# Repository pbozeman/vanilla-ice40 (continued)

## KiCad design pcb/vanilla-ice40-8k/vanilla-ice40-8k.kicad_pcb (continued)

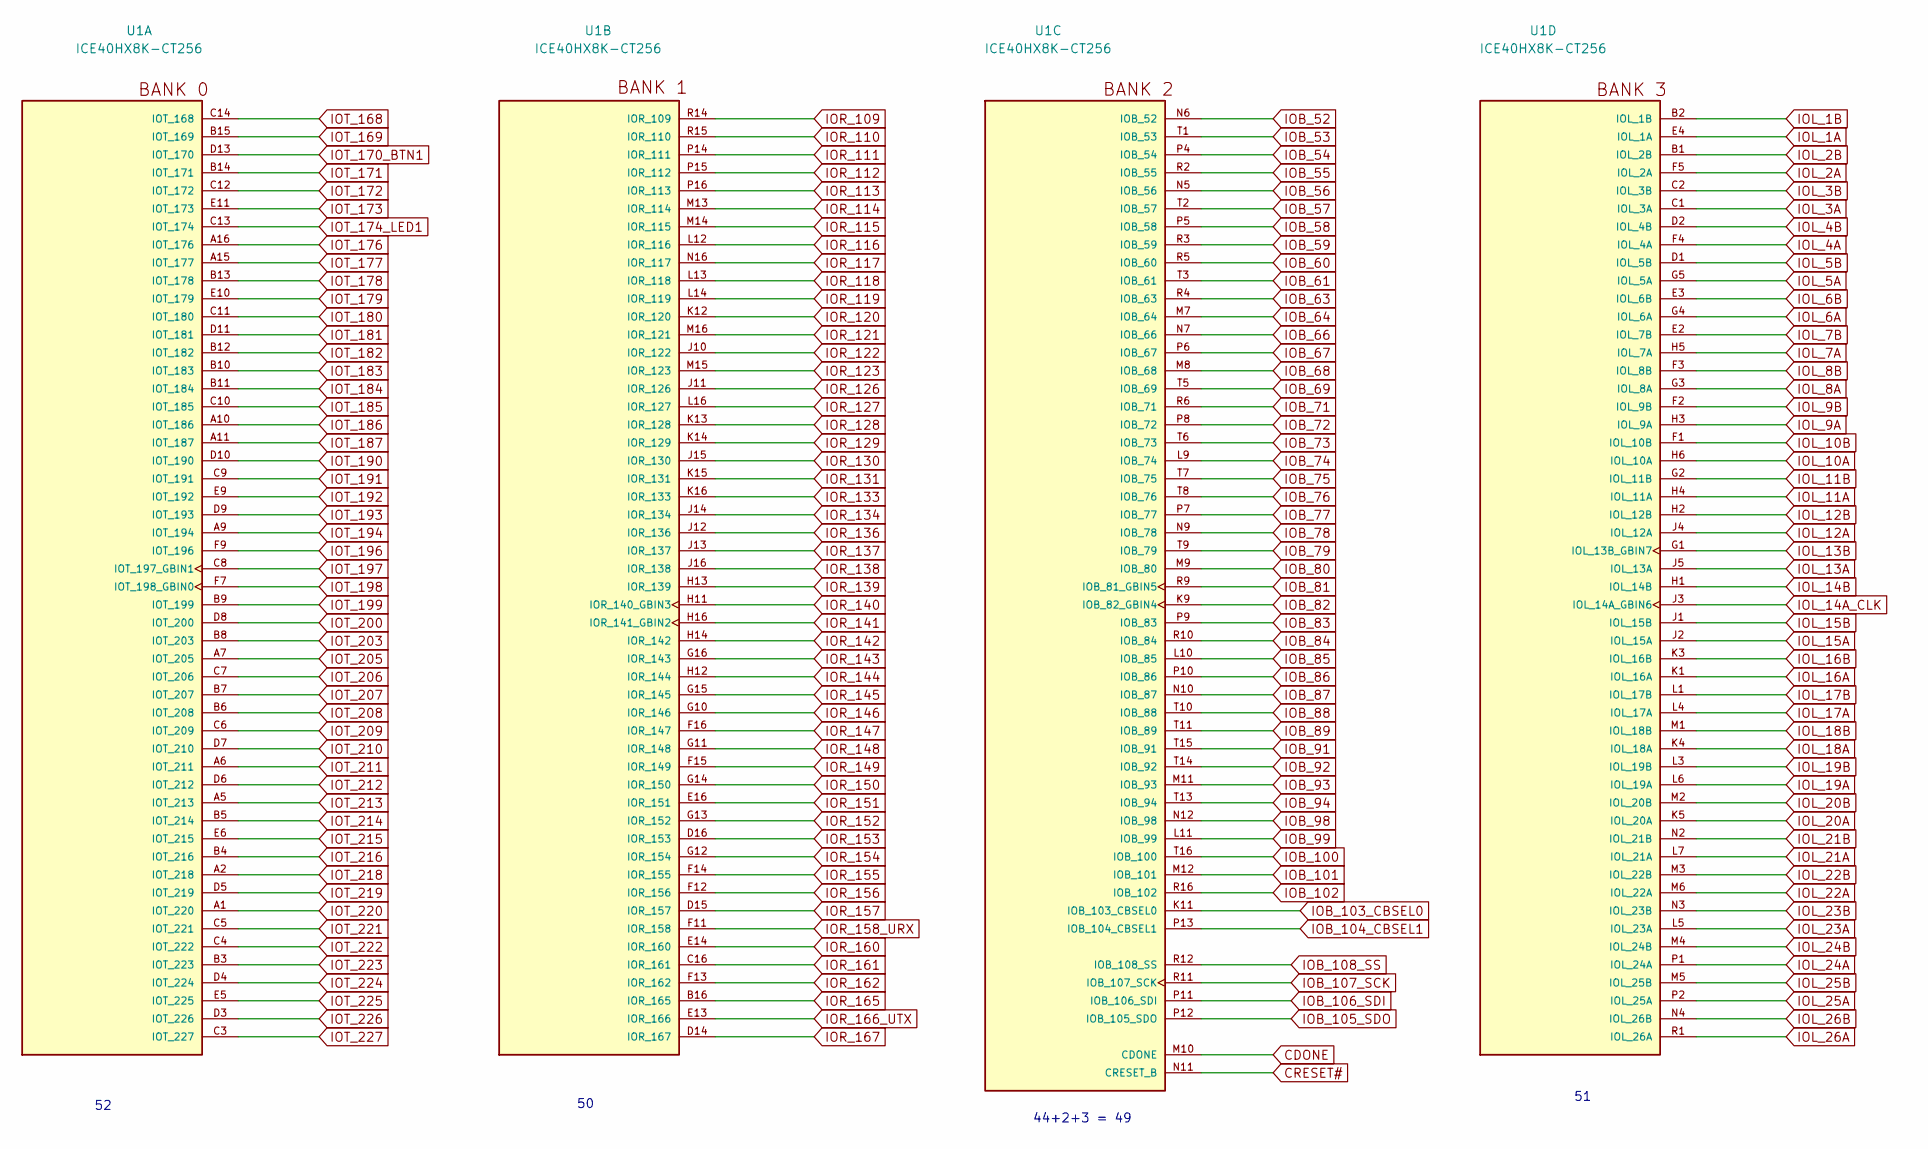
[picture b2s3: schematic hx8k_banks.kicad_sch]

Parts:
U1: ICE40HX8K-CT256; BGA256C80P16X16_1400X1400X170; Digi-Key Part Number 220-1575-ND

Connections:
CDONE: U1.M10 (CDONE); also elsewhere on the board
CRESET#: U1.N11 (CRESET_B); also elsewhere on the board
IOB_52: U1.N6 (IOB_52); also elsewhere on the board
IOB_53: U1.T1 (IOB_53); also elsewhere on the board
IOB_54: U1.P4 (IOB_54); also elsewhere on the board
IOB_55: U1.R2 (IOB_55); also elsewhere on the board
IOB_56: U1.N5 (IOB_56); also elsewhere on the board
IOB_57: U1.T2 (IOB_57); also elsewhere on the board
IOB_58: U1.P5 (IOB_58); also elsewhere on the board
IOB_59: U1.R3 (IOB_59); also elsewhere on the board
IOB_60: U1.R5 (IOB_60); also elsewhere on the board
IOB_61: U1.T3 (IOB_61); also elsewhere on the board
IOB_63: U1.R4 (IOB_63); also elsewhere on the board
IOB_64: U1.M7 (IOB_64); also elsewhere on the board
IOB_66: U1.N7 (IOB_66); also elsewhere on the board
IOB_67: U1.P6 (IOB_67); also elsewhere on the board
IOB_68: U1.M8 (IOB_68); also elsewhere on the board
IOB_69: U1.T5 (IOB_69); also elsewhere on the board
IOB_71: U1.R6 (IOB_71); also elsewhere on the board
IOB_72: U1.P8 (IOB_72); also elsewhere on the board
IOB_73: U1.T6 (IOB_73); also elsewhere on the board
IOB_74: U1.L9 (IOB_74); also elsewhere on the board
IOB_75: U1.T7 (IOB_75); also elsewhere on the board
IOB_76: U1.T8 (IOB_76); also elsewhere on the board
IOB_77: U1.P7 (IOB_77); also elsewhere on the board
IOB_78: U1.N9 (IOB_78); also elsewhere on the board
IOB_79: U1.T9 (IOB_79); also elsewhere on the board
IOB_80: U1.M9 (IOB_80); also elsewhere on the board
IOB_81: U1.R9 (IOB_81_GBIN5); also elsewhere on the board
IOB_82: U1.K9 (IOB_82_GBIN4); also elsewhere on the board
IOB_83: U1.P9 (IOB_83); also elsewhere on the board
IOB_84: U1.R10 (IOB_84); also elsewhere on the board
IOB_85: U1.L10 (IOB_85); also elsewhere on the board
IOB_86: U1.P10 (IOB_86); also elsewhere on the board
IOB_87: U1.N10 (IOB_87); also elsewhere on the board
IOB_88: U1.T10 (IOB_88); also elsewhere on the board
IOB_89: U1.T11 (IOB_89); also elsewhere on the board
IOB_91: U1.T15 (IOB_91); also elsewhere on the board
IOB_92: U1.T14 (IOB_92); also elsewhere on the board
IOB_93: U1.M11 (IOB_93); also elsewhere on the board
IOB_94: U1.T13 (IOB_94); also elsewhere on the board
IOB_98: U1.N12 (IOB_98); also elsewhere on the board
IOB_99: U1.L11 (IOB_99); also elsewhere on the board
IOB_100: U1.T16 (IOB_100); also elsewhere on the board
IOB_101: U1.M12 (IOB_101); also elsewhere on the board
IOB_102: U1.R16 (IOB_102); also elsewhere on the board
IOB_103_CBSEL0: U1.K11 (IOB_103_CBSEL0); also elsewhere on the board
IOB_104_CBSEL1: U1.P13 (IOB_104_CBSEL1); also elsewhere on the board
IOB_105_SDO: U1.P12 (IOB_105_SDO); also elsewhere on the board
IOB_106_SDI: U1.P11 (IOB_106_SDI); also elsewhere on the board
IOB_107_SCK: U1.R11 (IOB_107_SCK); also elsewhere on the board
IOB_108_SS: U1.R12 (IOB_108_SS); also elsewhere on the board
IOL_1A: U1.E4 (IOL_1A); also elsewhere on the board
IOL_1B: U1.B2 (IOL_1B); also elsewhere on the board
IOL_2A: U1.F5 (IOL_2A); also elsewhere on the board
IOL_2B: U1.B1 (IOL_2B); also elsewhere on the board
IOL_3A: U1.C1 (IOL_3A); also elsewhere on the board
IOL_3B: U1.C2 (IOL_3B); also elsewhere on the board
IOL_4A: U1.F4 (IOL_4A); also elsewhere on the board
IOL_4B: U1.D2 (IOL_4B); also elsewhere on the board
IOL_5A: U1.G5 (IOL_5A); also elsewhere on the board
IOL_5B: U1.D1 (IOL_5B); also elsewhere on the board
IOL_6A: U1.G4 (IOL_6A); also elsewhere on the board
IOL_6B: U1.E3 (IOL_6B); also elsewhere on the board
IOL_7A: U1.H5 (IOL_7A); also elsewhere on the board
IOL_7B: U1.E2 (IOL_7B); also elsewhere on the board
IOL_8A: U1.G3 (IOL_8A); also elsewhere on the board
IOL_8B: U1.F3 (IOL_8B); also elsewhere on the board
IOL_9A: U1.H3 (IOL_9A); also elsewhere on the board
IOL_9B: U1.F2 (IOL_9B); also elsewhere on the board
IOL_10A: U1.H6 (IOL_10A); also elsewhere on the board
IOL_10B: U1.F1 (IOL_10B); also elsewhere on the board
IOL_11A: U1.H4 (IOL_11A); also elsewhere on the board
IOL_11B: U1.G2 (IOL_11B); also elsewhere on the board
IOL_12A: U1.J4 (IOL_12A); also elsewhere on the board
IOL_12B: U1.H2 (IOL_12B); also elsewhere on the board
IOL_13A: U1.J5 (IOL_13A); also elsewhere on the board
IOL_13B: U1.G1 (IOL_13B_GBIN7); also elsewhere on the board
IOL_14A_CLK: U1.J3 (IOL_14A_GBIN6); also elsewhere on the board
IOL_14B: U1.H1 (IOL_14B); also elsewhere on the board
IOL_15A: U1.J2 (IOL_15A); also elsewhere on the board
IOL_15B: U1.J1 (IOL_15B); also elsewhere on the board
IOL_16A: U1.K1 (IOL_16A); also elsewhere on the board
IOL_16B: U1.K3 (IOL_16B); also elsewhere on the board
IOL_17A: U1.L4 (IOL_17A); also elsewhere on the board
IOL_17B: U1.L1 (IOL_17B); also elsewhere on the board
IOL_18A: U1.K4 (IOL_18A); also elsewhere on the board
IOL_18B: U1.M1 (IOL_18B); also elsewhere on the board
IOL_19A: U1.L6 (IOL_19A); also elsewhere on the board
IOL_19B: U1.L3 (IOL_19B); also elsewhere on the board
IOL_20A: U1.K5 (IOL_20A); also elsewhere on the board
IOL_20B: U1.M2 (IOL_20B); also elsewhere on the board
IOL_21A: U1.L7 (IOL_21A); also elsewhere on the board
IOL_21B: U1.N2 (IOL_21B); also elsewhere on the board
IOL_22A: U1.M6 (IOL_22A); also elsewhere on the board
IOL_22B: U1.M3 (IOL_22B); also elsewhere on the board
IOL_23A: U1.L5 (IOL_23A); also elsewhere on the board
IOL_23B: U1.N3 (IOL_23B); also elsewhere on the board
IOL_24A: U1.P1 (IOL_24A); also elsewhere on the board
IOL_24B: U1.M4 (IOL_24B); also elsewhere on the board
IOL_25A: U1.P2 (IOL_25A); also elsewhere on the board
IOL_25B: U1.M5 (IOL_25B); also elsewhere on the board
IOL_26A: U1.R1 (IOL_26A); also elsewhere on the board
IOL_26B: U1.N4 (IOL_26B); also elsewhere on the board
IOR_109: U1.R14 (IOR_109); also elsewhere on the board
IOR_110: U1.R15 (IOR_110); also elsewhere on the board
IOR_111: U1.P14 (IOR_111); also elsewhere on the board
IOR_112: U1.P15 (IOR_112); also elsewhere on the board
IOR_113: U1.P16 (IOR_113); also elsewhere on the board
IOR_114: U1.M13 (IOR_114); also elsewhere on the board
IOR_115: U1.M14 (IOR_115); also elsewhere on the board
IOR_116: U1.L12 (IOR_116); also elsewhere on the board
IOR_117: U1.N16 (IOR_117); also elsewhere on the board
IOR_118: U1.L13 (IOR_118); also elsewhere on the board
IOR_119: U1.L14 (IOR_119); also elsewhere on the board
IOR_120: U1.K12 (IOR_120); also elsewhere on the board
IOR_121: U1.M16 (IOR_121); also elsewhere on the board
IOR_122: U1.J10 (IOR_122); also elsewhere on the board
IOR_123: U1.M15 (IOR_123); also elsewhere on the board
IOR_126: U1.J11 (IOR_126); also elsewhere on the board
IOR_127: U1.L16 (IOR_127); also elsewhere on the board
IOR_128: U1.K13 (IOR_128); also elsewhere on the board
IOR_129: U1.K14 (IOR_129); also elsewhere on the board
IOR_130: U1.J15 (IOR_130); also elsewhere on the board
IOR_131: U1.K15 (IOR_131); also elsewhere on the board
IOR_133: U1.K16 (IOR_133); also elsewhere on the board
IOR_134: U1.J14 (IOR_134); also elsewhere on the board
IOR_136: U1.J12 (IOR_136); also elsewhere on the board
IOR_137: U1.J13 (IOR_137); also elsewhere on the board
IOR_138: U1.J16 (IOR_138); also elsewhere on the board
IOR_139: U1.H13 (IOR_139); also elsewhere on the board
IOR_140: U1.H11 (IOR_140_GBIN3); also elsewhere on the board
IOR_141: U1.H16 (IOR_141_GBIN2); also elsewhere on the board
IOR_142: U1.H14 (IOR_142); also elsewhere on the board
IOR_143: U1.G16 (IOR_143); also elsewhere on the board
IOR_144: U1.H12 (IOR_144); also elsewhere on the board
IOR_145: U1.G15 (IOR_145); also elsewhere on the board
IOR_146: U1.G10 (IOR_146); also elsewhere on the board
IOR_147: U1.F16 (IOR_147); also elsewhere on the board
IOR_148: U1.G11 (IOR_148); also elsewhere on the board
IOR_149: U1.F15 (IOR_149); also elsewhere on the board
IOR_150: U1.G14 (IOR_150); also elsewhere on the board
IOR_151: U1.E16 (IOR_151); also elsewhere on the board
IOR_152: U1.G13 (IOR_152); also elsewhere on the board
IOR_153: U1.D16 (IOR_153); also elsewhere on the board
IOR_154: U1.G12 (IOR_154); also elsewhere on the board
IOR_155: U1.F14 (IOR_155); also elsewhere on the board
IOR_156: U1.F12 (IOR_156); also elsewhere on the board
IOR_157: U1.D15 (IOR_157); also elsewhere on the board
IOR_158_URX: U1.F11 (IOR_158); also elsewhere on the board
IOR_160: U1.E14 (IOR_160); also elsewhere on the board
IOR_161: U1.C16 (IOR_161); also elsewhere on the board
IOR_162: U1.F13 (IOR_162); also elsewhere on the board
IOR_165: U1.B16 (IOR_165); also elsewhere on the board
IOR_166_UTX: U1.E13 (IOR_166); also elsewhere on the board
IOR_167: U1.D14 (IOR_167); also elsewhere on the board
IOT_168: U1.C14 (IOT_168); also elsewhere on the board
IOT_169: U1.B15 (IOT_169); also elsewhere on the board
IOT_170_BTN1: U1.D13 (IOT_170); also elsewhere on the board
IOT_171: U1.B14 (IOT_171); also elsewhere on the board
IOT_172: U1.C12 (IOT_172); also elsewhere on the board
IOT_173: U1.E11 (IOT_173); also elsewhere on the board
IOT_174_LED1: U1.C13 (IOT_174); also elsewhere on the board
IOT_176: U1.A16 (IOT_176); also elsewhere on the board
IOT_177: U1.A15 (IOT_177); also elsewhere on the board
IOT_178: U1.B13 (IOT_178); also elsewhere on the board
IOT_179: U1.E10 (IOT_179); also elsewhere on the board
IOT_180: U1.C11 (IOT_180); also elsewhere on the board
IOT_181: U1.D11 (IOT_181); also elsewhere on the board
IOT_182: U1.B12 (IOT_182); also elsewhere on the board
IOT_183: U1.B10 (IOT_183); also elsewhere on the board
IOT_184: U1.B11 (IOT_184); also elsewhere on the board
IOT_185: U1.C10 (IOT_185); also elsewhere on the board
IOT_186: U1.A10 (IOT_186); also elsewhere on the board
IOT_187: U1.A11 (IOT_187); also elsewhere on the board
IOT_190: U1.D10 (IOT_190); also elsewhere on the board
IOT_191: U1.C9 (IOT_191); also elsewhere on the board
IOT_192: U1.E9 (IOT_192); also elsewhere on the board
IOT_193: U1.D9 (IOT_193); also elsewhere on the board
IOT_194: U1.A9 (IOT_194); also elsewhere on the board
IOT_196: U1.F9 (IOT_196); also elsewhere on the board
IOT_197: U1.C8 (IOT_197_GBIN1); also elsewhere on the board
IOT_198: U1.F7 (IOT_198_GBIN0); also elsewhere on the board
IOT_199: U1.B9 (IOT_199); also elsewhere on the board
IOT_200: U1.D8 (IOT_200); also elsewhere on the board
IOT_203: U1.B8 (IOT_203); also elsewhere on the board
IOT_205: U1.A7 (IOT_205); also elsewhere on the board
IOT_206: U1.C7 (IOT_206); also elsewhere on the board
IOT_207: U1.B7 (IOT_207); also elsewhere on the board
IOT_208: U1.B6 (IOT_208); also elsewhere on the board
IOT_209: U1.C6 (IOT_209); also elsewhere on the board
IOT_210: U1.D7 (IOT_210); also elsewhere on the board
IOT_211: U1.A6 (IOT_211); also elsewhere on the board
IOT_212: U1.D6 (IOT_212); also elsewhere on the board
IOT_213: U1.A5 (IOT_213); also elsewhere on the board
IOT_214: U1.B5 (IOT_214); also elsewhere on the board
IOT_215: U1.E6 (IOT_215); also elsewhere on the board
IOT_216: U1.B4 (IOT_216); also elsewhere on the board
IOT_218: U1.A2 (IOT_218); also elsewhere on the board
IOT_219: U1.D5 (IOT_219); also elsewhere on the board
IOT_220: U1.A1 (IOT_220); also elsewhere on the board
IOT_221: U1.C5 (IOT_221); also elsewhere on the board
IOT_222: U1.C4 (IOT_222); also elsewhere on the board
IOT_223: U1.B3 (IOT_223); also elsewhere on the board
IOT_224: U1.D4 (IOT_224); also elsewhere on the board
IOT_225: U1.E5 (IOT_225); also elsewhere on the board
IOT_226: U1.D3 (IOT_226); also elsewhere on the board
IOT_227: U1.C3 (IOT_227); also elsewhere on the board

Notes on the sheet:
44+2+3 = 49

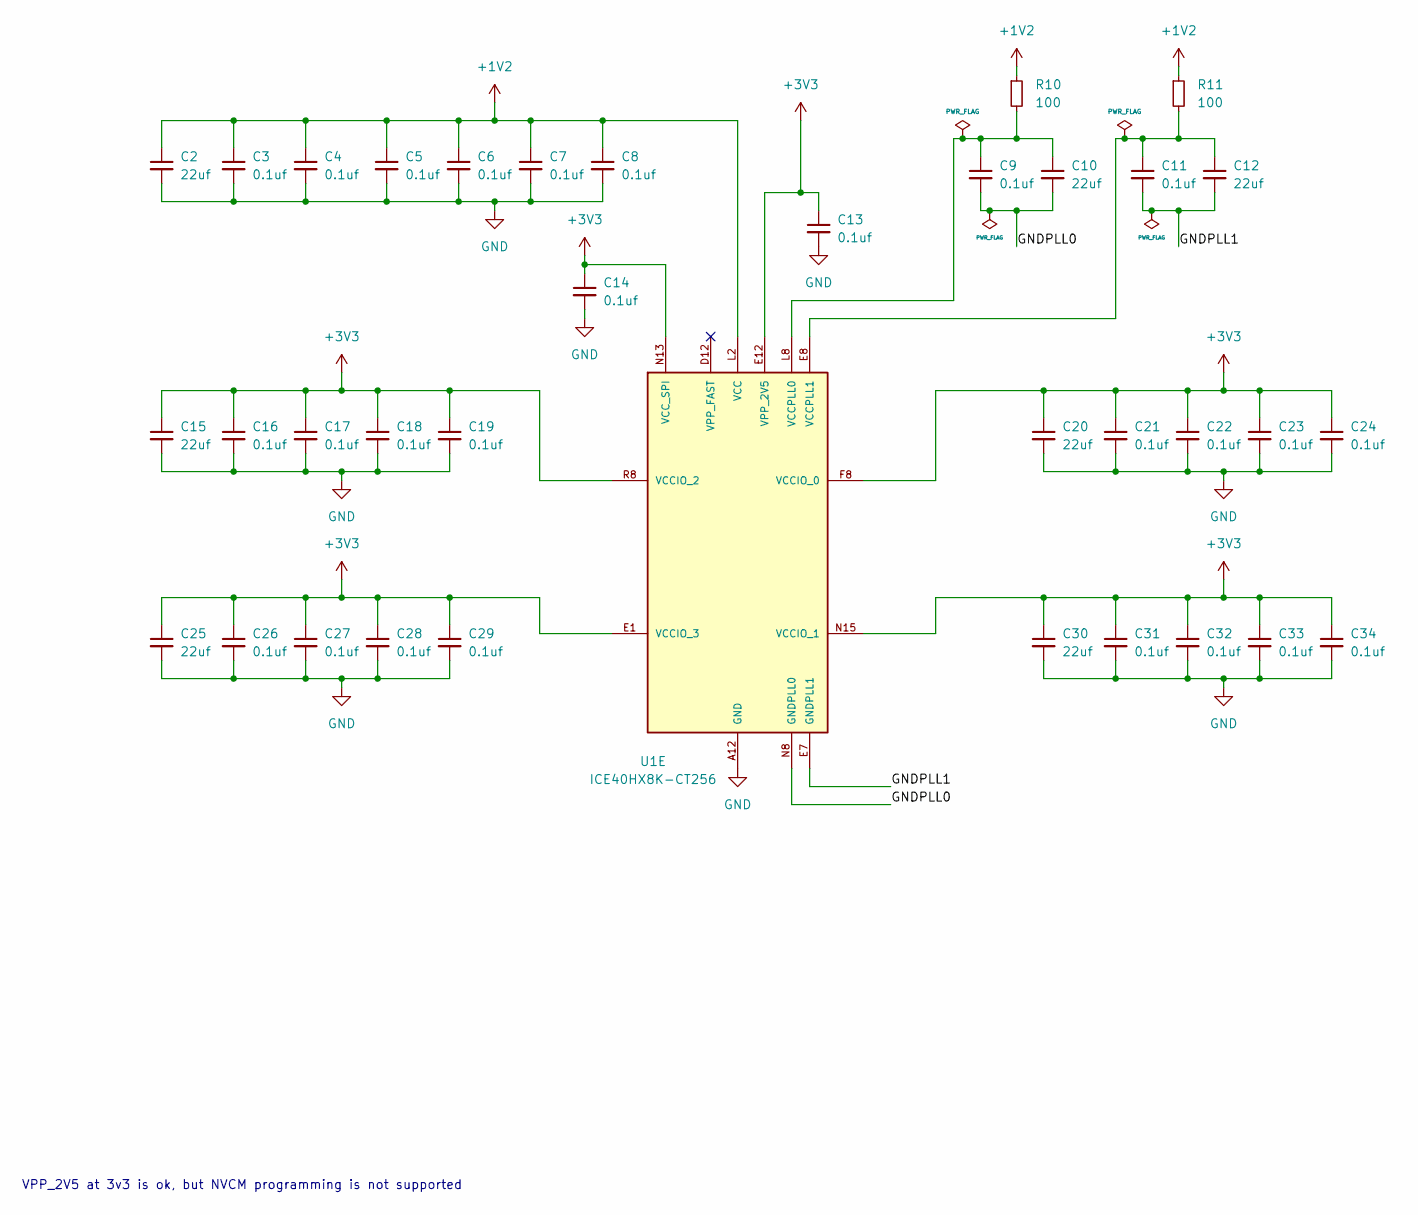
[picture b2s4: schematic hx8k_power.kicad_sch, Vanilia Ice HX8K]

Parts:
C2, C10, C12, C15, C20, C25, C30: 22uf; C_0603_1608Metric; LCSC Part # C59461
C3, C4, C5, C6, C7, C8, C9, C11, C13, C14, C16, C17, C18, C19, C21, C22, C23, C24, C26, C27, C28, C29, C31, C32, C33, C34: 0.1uf; C_0201_0603Metric; LCSC Part # C160831
R10, R11: 100; R_0603_1608Metric; LCSC Part # C22775
U1: ICE40HX8K-CT256; BGA256C80P16X16_1400X1400X170; LCSC Part # C1521993

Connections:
+1V2: C2.1, C3.1, C4.1, C5.1, C6.1, C7.1, C8.1, R10.1, R11.1, U1.A14 (VCC), U1.F6 (VCC), U1.F10 (VCC), U1.K6 (VCC), U1.K10 (VCC), U1.L2 (VCC); also elsewhere on the board
+3V3: C13.1, C14.1, C15.1, C16.1, C17.1, C18.1, C19.1, C20.1, C21.1, C22.1, C23.1, C24.1, C25.1, C26.1, C27.1, C28.1, C29.1, C30.1, C31.1, C32.1, C33.1, C34.1, U1.A3 (VCCIO_0), U1.A8 (VCCIO_0), U1.A13 (VCCIO_0), U1.C15 (VCCIO_1), U1.E1 (VCCIO_3), U1.E12 (VPP_2V5), U1.F8 (VCCIO_0), U1.G6 (VCCIO_3), U1.H10 (VCCIO_1), U1.H15 (VCCIO_1), U1.J6 (VCCIO_3), U1.K8 (VCCIO_2), U1.N1 (VCCIO_3), U1.N13 (VCC_SPI), U1.N15 (VCCIO_1), U1.P3 (VCCIO_2), U1.R8 (VCCIO_2), U1.R13 (VCCIO_2); also elsewhere on the board
/hx8k power/GNDPLL0: C9.2, C10.2, U1.N8 (GNDPLL0)
/hx8k power/GNDPLL1: C11.2, C12.2, U1.E7 (GNDPLL1)
GND: C2.2, C3.2, C4.2, C5.2, C6.2, C7.2, C8.2, C13.2, C14.2, C15.2, C16.2, C17.2, C18.2, C19.2, C20.2, C21.2, C22.2, C23.2, C24.2, C25.2, C26.2, C27.2, C28.2, C29.2, C30.2, C31.2, C32.2, C33.2, C34.2, U1.A4 (GND), U1.A12 (GND), U1.E15 (GND), U1.G7 (GND), U1.G8 (GND), U1.G9 (GND), U1.H7 (GND), U1.H8 (GND), U1.H9 (GND), U1.J7 (GND), U1.J8 (GND), U1.J9 (GND), U1.K2 (GND), U1.K7 (GND), U1.L15 (GND), U1.R7 (GND), U1.T4 (GND), U1.T12 (GND); also elsewhere on the board
unnamed: C9.1, C10.1, R10.2, U1.L8 (VCCPLL0)
unnamed: C11.1, C12.1, R11.2, U1.E8 (VCCPLL1)

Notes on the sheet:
VPP_2V5 at 3v3 is ok, but NVCM programming is not supported

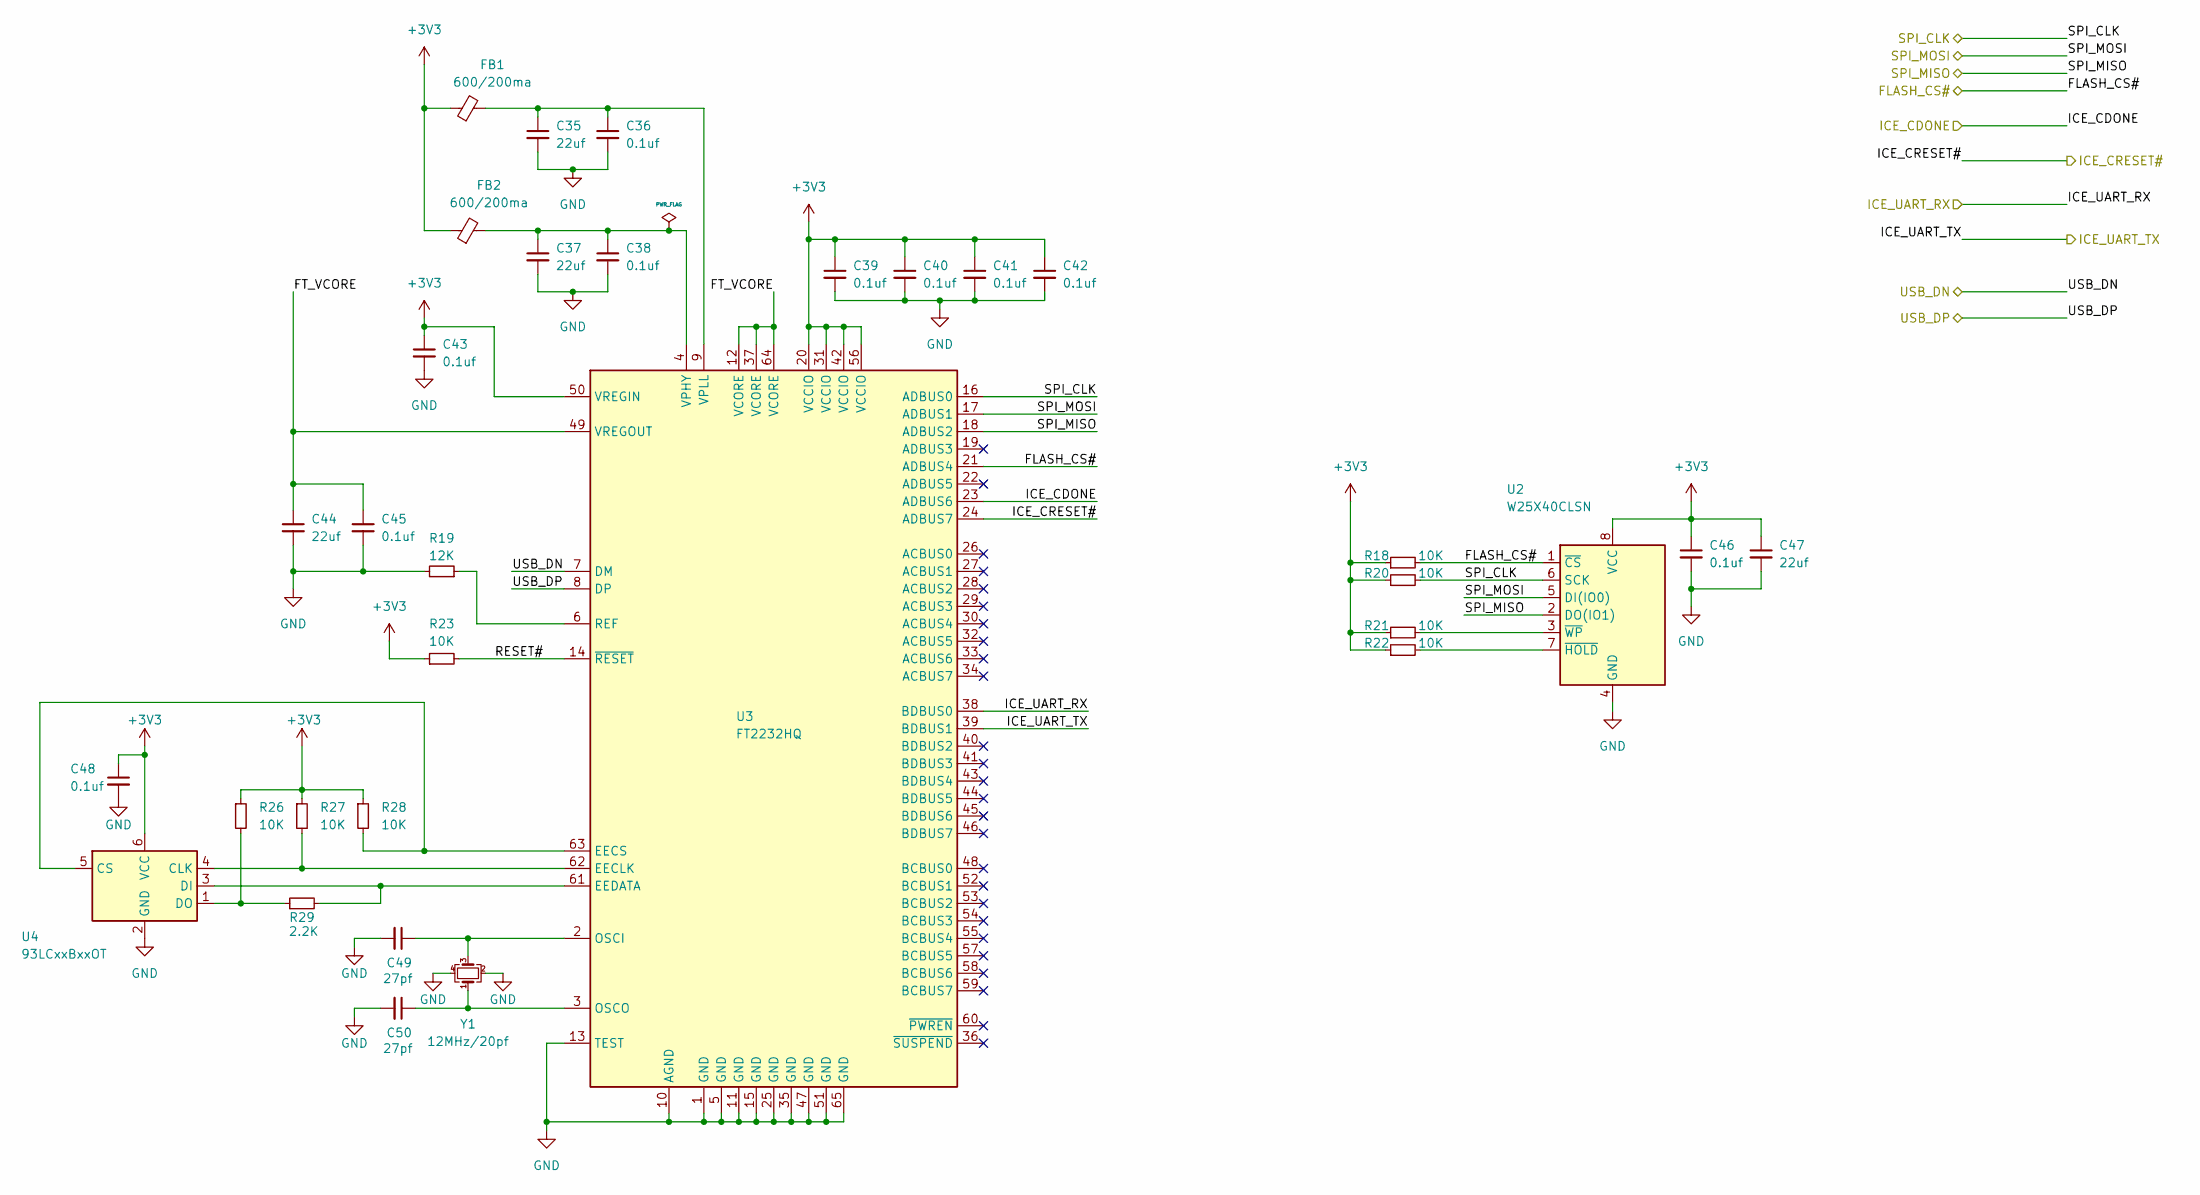
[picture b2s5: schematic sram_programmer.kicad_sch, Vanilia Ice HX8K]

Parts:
C35, C37, C44, C47: 22uf; C_0603_1608Metric; LCSC Part # C59461
C36, C38, C39, C40, C41, C42, C43, C45, C46, C48: 0.1uf; C_0402_1005Metric; LCSC Part # C1525
C49, C50: 27pf; C_0402_1005Metric; LCSC Part # C1555
FB1, FB2: 600/200ma; L_0603_1608Metric; LCSC Part # C1002
R18, R20, R21, R22, R23, R26, R27, R28: 10K; R_0603_1608Metric; LCSC Part # C25804
R19: 12K; R_0603_1608Metric; LCSC Part # C22790
R29: 2.2K; R_0603_1608Metric; LCSC Part # C4190
U2: W25X40CLSN; SOIC-8_3.9x4.9mm_P1.27mm; LCSC Part # C19617
U3: FT2232HQ; LCSC Part # C193662
U4: 93LCxxBxxOT; SOT-23-6; LCSC Part # C190271
Y1: 12MHz/20pf; Crystal_SMD_3225-4Pin_3.2x2.5mm; LCSC Part # C9002

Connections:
+3V3: C39.1, C40.1, C41.1, C42.1, C43.1, C46.1, C47.1, C48.1, FB1.1, FB2.1, R18.1, R20.1, R21.1, R22.1, R23.1, R26.1, R27.1, R28.1, U2.8 (VCC), U3.20 (VCCIO), U3.31 (VCCIO), U3.42 (VCCIO), U3.50 (VREGIN), U3.56 (VCCIO), U4.6 (VCC); also elsewhere on the board
/USB_DN: U3.7 (DM); also elsewhere on the board
/USB_DP: U3.8 (DP); also elsewhere on the board
/sram programmer/FT_VCORE: C44.1, C45.1, U3.12 (VCORE), U3.37 (VCORE), U3.49 (VREGOUT), U3.64 (VCORE)
/sram programmer/RESET#: R23.2, U3.14 (~RESET)
CDONE: U3.23 (ADBUS6); also elsewhere on the board
CRESET#: U3.24 (ADBUS7); also elsewhere on the board
GND: C35.2, C36.2, C37.2, C38.2, C39.2, C40.2, C41.2, C42.2, C43.2, C44.2, C45.2, C46.2, C47.2, C48.2, C49.2, C50.2, R19.2, U2.4 (GND), U3.1 (GND), U3.5 (GND), U3.10 (AGND), U3.11 (GND), U3.13 (TEST), U3.15 (GND), U3.25 (GND), U3.35 (GND), U3.47 (GND), U3.51 (GND), U3.65 (GND), U4.2 (GND), Y1.2, Y1.4; also elsewhere on the board
IOB_105_SDO: U2.5 (DI(IO0)), U3.17 (ADBUS1); also elsewhere on the board
IOB_106_SDI: U2.2 (DO(IO1)), U3.18 (ADBUS2); also elsewhere on the board
IOB_107_SCK: R20.2, U2.6 (SCK), U3.16 (ADBUS0); also elsewhere on the board
IOB_108_SS: R18.2, U2.1 (~CS), U3.21 (ADBUS4); also elsewhere on the board
IOR_158_URX: U3.38 (BDBUS0); also elsewhere on the board
IOR_166_UTX: U3.39 (BDBUS1); also elsewhere on the board
unnamed: R22.2, U2.7 (~HOLD)
unnamed: R21.2, U2.3 (~WP)
unnamed: R27.2, U3.62 (EECLK), U4.4 (CLK)
unnamed: R28.2, U3.63 (EECS), U4.5 (CS)
unnamed: R29.2, U3.61 (EEDATA), U4.3 (DI)
unnamed: C49.1, U3.2 (OSCI), Y1.3
unnamed: C50.1, U3.3 (OSCO), Y1.1
unnamed: R19.1, U3.6 (REF)
unnamed: C37.1, C38.1, FB2.2, U3.4 (VPHY)
unnamed: C35.1, C36.1, FB1.2, U3.9 (VPLL)
unnamed: R26.2, R29.1, U4.1 (DO)
